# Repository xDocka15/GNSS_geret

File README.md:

# GNSS_Geret_V1

[3D model](https://github.com/xDocka15/GNSS_geret/blob/main/V1/3D_Print/stl/board.stl)

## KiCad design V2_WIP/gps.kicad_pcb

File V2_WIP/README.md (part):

# Zadanie pre GNSS Geret v2025

Dokument popisuje zmeny/upravy v elektronike gnss-geret z 2024 tak aby vznikla
jednodoskova prenostitelna verzia.

## Strucny opis zmien

Cielom je dosiahnut vyssiu integraciu, mensie rozmery a odstranit nedostatky
z predchadzajucej verzie.

Hlavne zmeny:

* \[x] Z troch DPS zredukovat len na jednu dosku.
* \[X] Povodnu hotovu procesorovu dosku FireBeetle2 nahradit samostatnymi obvodmi
  priamo na DPS a usetrit tym miesto:

  * \[x] Pouzit rovnaky ESP32-WROOM-32E modul
  * \[x] USB/UART prevodnik pre programovanie a ladenie ESP32 aj s DTR+RST pre programovanie
  * \[x] Menic napatia z baterie na 3V3
  * \[x] Nabijaci obvod pre bateriu (lepsi ako na FireBeetle2)

* \[x] Doplnit flash pre zaznam dat.
* \[ ] Lepsia citatelnost displeja s casom.

Vacsina suciastok zostava zachovana, zhodna s verziou v2024.

## Nove suciastky

### ESP32

Zvolit modul:

* ESP32-WROVER-E-N16R8 - trosku vacsi rozmer, ale ma vacsiu pamat, vyvody len z dvoch stran.
* \[x] ESP32-WROOM-32E-N16R2 - mensi rozmer, mensia pamat, vyvody z troch stran.

Umiestnit antenou ku okraju DPS. Pod vstavanou antenou je potrebne odstranit
oblast zeme v jednotlivych vrstvach DPS tak aby nedoslo ku zatieneniu anteny (napr.
vrstvou GND, vid. keepout zone v datasheete). Idealne vyfrezovat z plosaku.

Doska WROVER sa pripajkuje priamo na hlavny DPS.

Nerozpustat obsah WROOM modulu priamo na hlavny DPS, odovodnenie:

* nepredpokladam, ze by sa podarilo dosiahnut vasiu mieru integracie ako samotnemu
  vyrobcovi Espressif - t.j. neusetri sa miesto na DPS
* rucne osadzovanie by bolo skoro nemozne
* vyzadovalo by to ozivit zapojenie aj samotneho procesora
* neskor by ake kolvek chyby mohli mat pricinu bud v osadeni alebo navrhu zapojenia
  procesora

### USB/UART prevodnik

Pouzit niektory z casto pouzivanych USB na UART prevodnikov pre ESP procesory.
Napr. CH340K (bol pouzity aj na FireBeetle2) alebo CP2104, ...

Dolezite je pripojit aj DTR a RTS na GPIO0 a RST aby sa dal procesor uviest do
programovacieho rezimu cez USB.

Inspirovat sa zapojenim podla schemy ku FireBeetle2 alebo napr. ku LiLyGo T-Call.

### SPI Flash

Zapracovat "velku" SPI flash, ktora sa bude pouzivat na zaznam udajov z letu.
Napr. 128Mbit (16MB) [Winbond W25Q128FV](https://www.winbond.com/hq/product/code-storage-flash-memory/serial-nor-flash/?__locale=en&partNo=W25Q128FV).
Pripojit na SPI rozhranie.

* \[x] TODO: vyspecifikovat, na ktore piny procesora pripojit. Ktore z dvoch SPI rozhrani je volne?

### Nabijaci resp. power-management modul

Na napajanie bude pouzity jeden clanok Li-Ion baterie (v letectve sa nepouzivaju Li-Pol).
Mal by obsahovat:

* \[x] moznost vycitat cez komunikaciu (idealne I2C) stav nabijania (miera vybita)
* \[x] coulomb counter na meranie kapacity bateria
* \[x] meranie napatia baterie

Zapracovat modul na sledovanie kapacity LiXy batetie MAX17043.
https://techfun.sk/produkt/max17043-i2c-modul-pre-sledovanie-stavu-baterie-1s/

https://www.sparkfun.com/mikroe-charger-2-click.html
Coulomb counter TC3100 + nabijaci obvod IP5306-I2C.
https://electronics.stackexchange.com/questions/17463/help-on-stc3100-calculations
https://github.com/danirebollo/ArduinoSTC3100

* \[x] TODO: upresnit.

### Tlacidlo

Pridat nove mikro-tlacidlo niekam na pravu prednu stranu.

* \[x] TODO: Vyspecifikovat tlacidlo, umiestnenie a pripojenie.

### Indikacna LED

Pridat SMD modru LED na stranu DPS s displejmi. Pouzije sa na zakladnu indikaciu
a ladenie SW. Spolu s LED na rovnaky ovladaci pin procesora pripojit aj test-pad.
Nakolko su vsetky ostatne LED pripojene len cez komunikacne rozhranie, tato bude
urcite fungovat vzdy.
Zapojit na GPIOxy voci GND.

* \[x] TODO: Urcit, na ktory GPIO pin.

### Senzor osvetlenia

Doplnit senzor osvetlenia a automaticky upravovat jas.
Umiestnit ho do vnutorneho rohu kde sa stretava maly dolny displej a stredny velky displej
na pravej strane (na opacnej ako je encoder, aby sa rukou nezakryl).
V kryte sa na danom mieste urobi vybratie, cez ktore (a cez foliu) bude prenikat okolite svetlo
az ku DPS.

* \[x] TODO: Pouzit jednoduchy fototranzistor? Vyspecifikovat.

## Upravy

Vo verzii v2024 boli na DPS/scheme identifikovane nesledujuce body na zlepsenie:

* \[x] Doplnit USB iface pre gnss (3v3 urovne, pripojit vdd\_usb)
  Zvazit umiestnenie plnohodnotneho USB micro-B konektora otoceneho ku okraju DPS
  kvoli servisnemu pristupu do GNSS modulu. Pouzit uhlovy konektor o 90st zarovnany
  s okrajom DPS. Pristupny bude len po vybrati DPS z krabicky.
* \[x] Pridat odrusovaci kondik na tlacidlo tocitka.

  * TODO: Vyspecifikovat.

* \[x] Na vstup A a B z encodra doplnit pull-up rezistory 10k na 3V3.
* \[x] Do footprintu encodera pridat aj diery pre upevnovacie otvory (pajkovatelne, spojene s GND)
* \[x] Pouzit iny typ stredneho 4-ciferneho displeja:

  * Na v2024 bol pouzity typ so spolocnou anodou (KW4-804AGB).

    * Radic HT16K33 je koncipovany tak, ze:
    * cez samostatne anody dokaze do LED pustit 20mA
    * ces spolocnu katodu dokaze preniest 8x 20mA
    * kvoli tomu nebolo mozne vybudit LED na maximalny jas co sa prejavilo na zlej
      citatelnosti za slnecneho svetla.

  * \[x] Vo v2025 pouzit model so spolocnou katodou (KW4-804CGB).

    * Tomu sa musi prisposobit aj zapojenie jednotlivych segmentov (po vzore maleho displeja).
    * \[x] TODO: vyspecifikovat zapojenie displeja.

* \[x] Pouzit USB-C konektor, zapojenie rovnake ako na FireBeetle2.
* \[x] Ku GNSS modulu pripojit aj zalohovaciu bateriu pre RTC.

### Chybajuce veci

Vo verzii v2024 chybali nasledujuce veci, ktore su aplikovatelne aj na v2025:

* \[x] Na 5V vetvu pridat velky stabilizacny kondik 470u/16V.
* Doplnit oznacenie D2 do schemy.
* \[x] Pridat test pad s GND (na pripojenie sondy multimetra/osciloskopu).

### Navrh DPS

Pri navrhu DPS zohladnit nasledujuce pripomienky:

* \[x] Pri ploskach spojenych s GND nastavit uzsie (tensie) mostiky, ktore prepajaju
  plosku s okolitou "vyliatou" plochou, resp. s vrstvou GND. Pri rucnom pajkovani
  sa cez mensie mostiky odvadza menej tepla do susednej velkej medenej plochy
  a suciastky sa lahsie osadzuju.
* \[x] Popisok konektora dat dalej od samotnej suciastky (aby sa po osadeni nezakryl).
* \[x] Zvacsit diery pre hlavny vypinac (bolo treba zbrusit z pinov).

  * \[x] TODO: diery pre kontakty alebo upevnovacie diery?

* \[x] Mensie diery pre kolikove konektory (ak budu pouzite, boli volne a dali sa osadit krivo :)
* \[x] Doplnit popisky ku test-padom "TPx" aby sa dali lahsie sparovat so schemou.
* \[ ] Pri vyrobe pouzit ciernu farbu plosaku, nie zelenu. Cierne pozadie zlepsi
  citatelnost 7-seg displejov.
* \[x] Niektore TP presunut ku okrajom DPS, tak aby boli dostupne z oboch stran DPS
  a neboli zakryte suciastkami (napr. displejmi):

  * TP6 (5V)
  * TPxy (3V3, pridat)
  * TPxy (GND, pridat)

* \[x] Antenny konektor moze byt bud SMA alebo U.FL (IPEX)

  * Na DPS cez seba prekryt plosky pre oba typy konektorov
  * Vid. footprint: https://meshtastic.org/assets/images/t-beam-sx1262-3dc0a8d2d866b06b04a457567063e034.webp
  * Bud sa osadi SMA konektor (uhlovy alebo priamy) alebo sa osadi U.FL konektor
    a antena sa zabuduje priamo do skatulky.

* Pri rozmiestnovani suciastok je mozne umiestnit niektore aj pod maly dolny
  displej z TOP strany.

  * Aby bol displej v rovine s RGB displejmi, musi byt osadeny co najdalej od DPS.
  * Tym vznikne pod displejom pohodlny priestor pre SMD rezistory, kondiky, atp...

    * \[ ] TODO: zmerat vzdialenost od DPS po display.

## Mechanicke upravy

* Zachovat rozostup aj velkosti montaznych dier v troch rohoch.

  * Pouziju sa bud na uchytenie do pristrojoveho panela v lietadle alebo na
    uchytenie krabicky.

* Ine montazne diery nebudu potrebne. Bateria sa osadi do drziaka v krabicke.
* Zachovat umiestnenie antenneho konektora GPS na okraji plosaku aby sa mohol
  pouzit aj uhlovy konektor a externa antena.

# Pripomienky k v2024

Releventnost nasledujuce pripomienok ku verzii v2024 a ich aplikovatelnost aj na
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
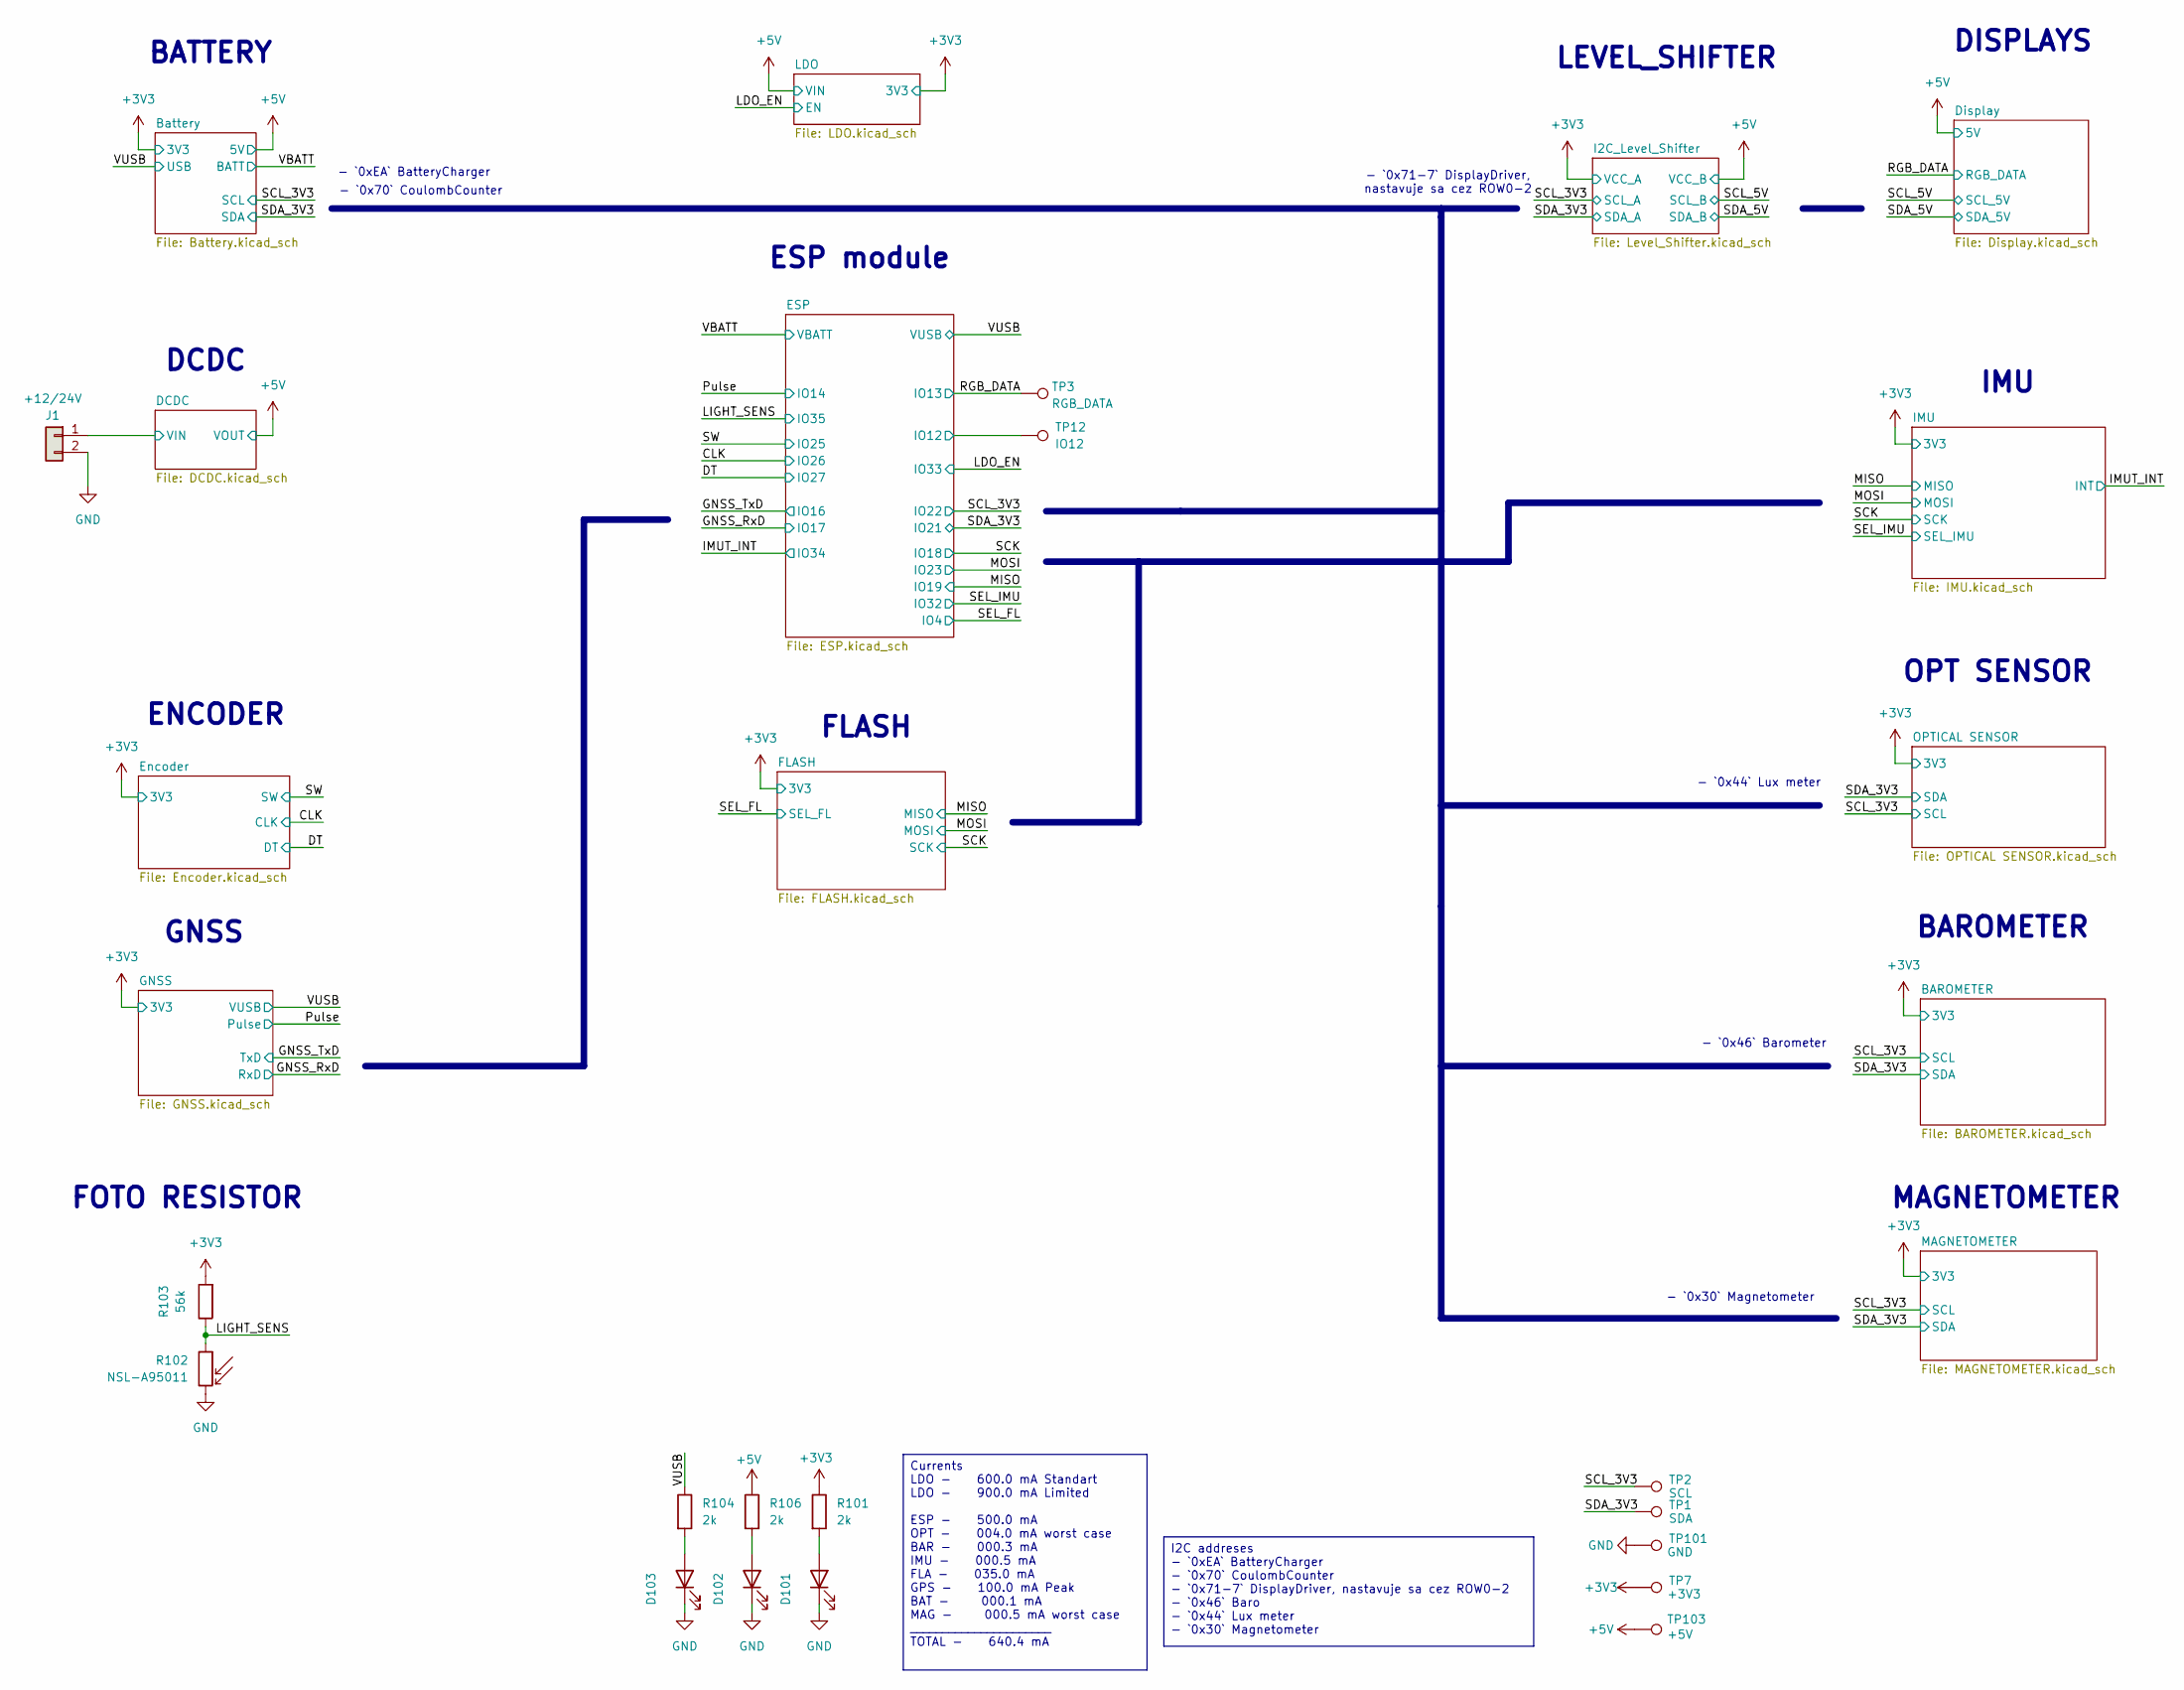
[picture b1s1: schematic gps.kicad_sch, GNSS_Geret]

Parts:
D101, D102, D103: D_0603_1608Metric_Pad1.05x0.95mm_HandSolder
J1: +12/24V; PhoenixContact_GMSTBVA_2,5_2-G-7,62_1x02_P7.62mm_Vertical
R101, R104, R106: 2k; R_0603_1608Metric_Pad0.98x0.95mm_HandSolder
R102: NSL-A95011; R_LDR_5.1x4.3mm_P3.4mm_Vertical
R103: 56k; R_0603_1608Metric_Pad0.98x0.95mm_HandSolder
TP1: SDA; TestPoint_Pad_D1.0mm
TP2: SCL; TestPoint_Pad_D1.0mm
TP3: RGB_DATA; TestPoint_Pad_D1.0mm
TP7: +3V3; TestPoint_Pad_D1.0mm
TP12: IO12; TestPoint_Pad_D1.0mm
TP101: GND; TestPoint_THTPad_D2.5mm_Drill1.2mm
TP103: +5V; TestPoint_Pad_D1.0mm

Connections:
+3V3: R101.1, R103.2, TP7.1 (1_1); also elsewhere on the board
+5V: R106.1, TP103.1 (1_1); also elsewhere on the board
/DCDC/VIN: J1.1; also elsewhere on the board
/ESP/IO12: TP12.1 (1_1); also elsewhere on the board
/LIGHT_SENS: R102.1, R103.1; also elsewhere on the board
/RGB_DATA: TP3.1 (1_1); also elsewhere on the board
/SCL_3V3: TP2.1 (1_1); also elsewhere on the board
/SDA_3V3: TP1.1 (1_1); also elsewhere on the board
/VUSB: R104.1; also elsewhere on the board
GND: D101.1 (K), D102.1 (K), D103.1 (K), J1.2, R102.2, TP101.1 (1_1); also elsewhere on the board
unnamed: D101.2 (A), R101.2
unnamed: D102.2 (A), R106.2
unnamed: D103.2 (A), R104.2

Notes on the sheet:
ESP module
- `0x44` Lux meter
BATTERY
GNSS
DCDC
OPT SENSOR
MAGNETOMETER
FOTO RESISTOR
FLASH
DISPLAYS
- `0xEA` BatteryCharger
- `0x71-7` DisplayDriver, nastavuje sa cez ROW0-2
- `0x46` Barometer
BAROMETER
- `0x70` CoulombCounter
- `0x30` Magnetometer
ENCODER
LEVEL_SHIFTER
IMU
Currents LDO - 600.0 mA Standart LDO - 900.0 mA Limited ESP - 500.0 mA OPT - 004.0 mA worst case BAR - 000.3 mA IMU - 000.5 mA FLA - 035.0 mA GPS - 100.0 mA Peak BAT - 000.1 mA MAG - 000.5 mA worst case ______________________ TOTAL - 640.4 mA
I2C addreses - `0xEA` BatteryCharger - `0x70` CoulombCounter - `0x71-7` DisplayDriver, nastavuje sa cez ROW0-2 - `0x46` Baro - `0x44` Lux meter - `0x30` Magnetometer

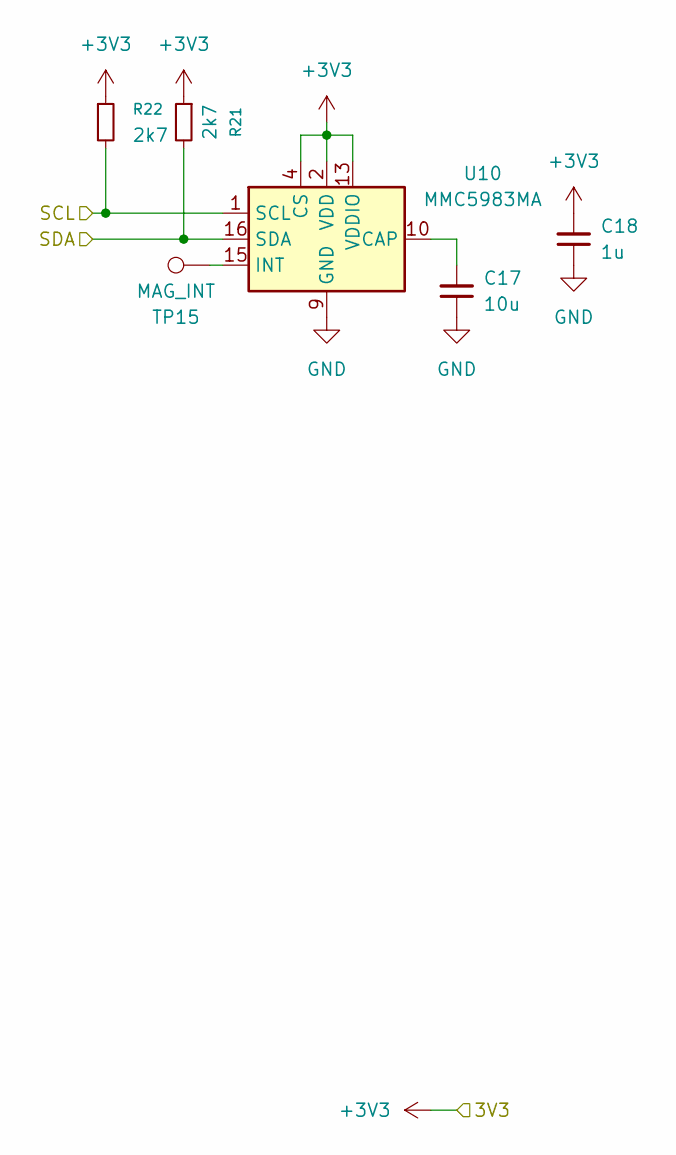
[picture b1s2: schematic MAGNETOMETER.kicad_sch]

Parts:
C17: 10u; C_0603_1608Metric_Pad1.08x0.95mm_HandSolder
C18: 1u; C_0603_1608Metric_Pad1.08x0.95mm_HandSolder
R21, R22: 2k7; R_0603_1608Metric_Pad0.98x0.95mm_HandSolder
TP15: MAG_INT; TestPoint_Pad_D1.0mm
U10: MMC5983MA; LGA-16_3x3mm_P0.5mm

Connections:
+3V3: C18.2, R21.1, R22.1, U10.2 (VDD), U10.4 (CS), U10.13 (VDDIO); also elsewhere on the board
/SCL_3V3: R22.2, U10.1 (SCL); also elsewhere on the board
/SDA_3V3: R21.2, U10.16 (SDA); also elsewhere on the board
GND: C17.1, C18.1, U10.9 (GND), U10.11 (GND); also elsewhere on the board
unnamed: C17.2, U10.10 (CAP)
unnamed: TP15.1 (1_1), U10.15 (INT)

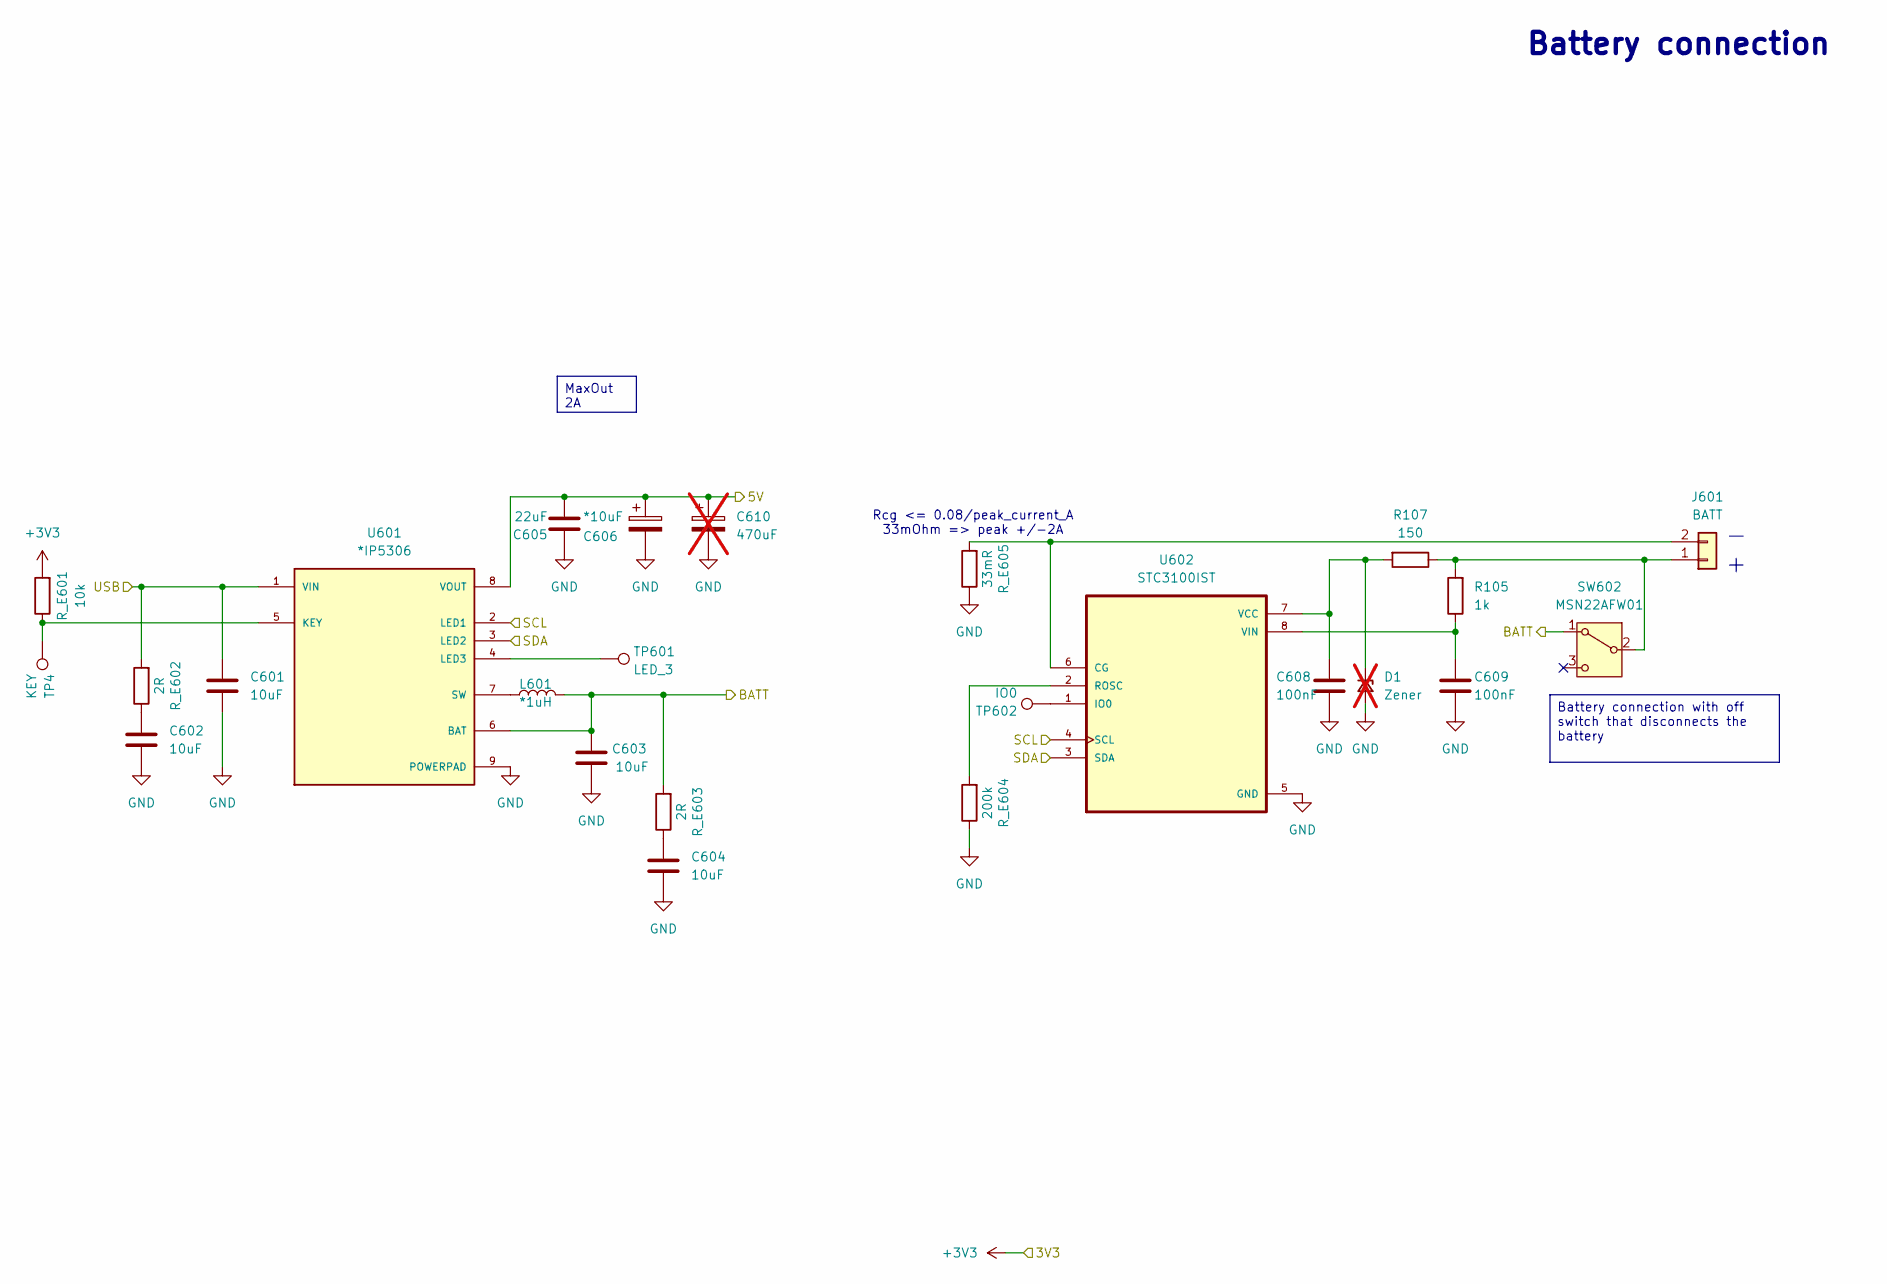
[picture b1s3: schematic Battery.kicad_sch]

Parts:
C601, C602, C603, C604: 10uF; C_0603_1608Metric_Pad1.08x0.95mm_HandSolder
C605: 22uF; C_0603_1608Metric_Pad1.08x0.95mm_HandSolder
C606: *10uF; CP_EIA-3528-21_Kemet-B_HandSolder
C608, C609: 100nF; C_0603_1608Metric_Pad1.08x0.95mm_HandSolder
C610: 470uF; C_Elec_6.3x7.7; not fitted
D1: Zener; D_SOD-523; not fitted
J601: BATT; Molex_PicoBlade_53398-0271_1x02-1MP_P1.25mm_Vertical
L601: *1uH; L_1008_2520Metric_Pad1.43x2.20mm_HandSolder
R105: 1k; R_0603_1608Metric_Pad0.98x0.95mm_HandSolder
R107: 150; R_0603_1608Metric_Pad0.98x0.95mm_HandSolder
R_E601: 10k; R_0603_1608Metric_Pad0.98x0.95mm_HandSolder
R_E602, R_E603: 2R; R_0603_1608Metric_Pad0.98x0.95mm_HandSolder
R_E604: 200k; R_0603_1608Metric_Pad0.98x0.95mm_HandSolder
R_E605: 33mR; R_0603_1608Metric_Pad0.98x0.95mm_HandSolder
SW602: MSN22AFW01
TP4: KEY; TestPoint_Pad_D1.0mm
TP601: LED_3; TestPoint_Pad_D1.0mm
TP602: IO0; TestPoint_Pad_D1.0mm
U601: *IP5306; SOP127P600X165-9N; PARTREV 1.31
U602: STC3100IST; SOIC65P490X110-8N

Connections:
+3V3: R_E601.2; also elsewhere on the board
+5V: C605.2, C606.1, C610.1, U601.8 (VOUT); also elsewhere on the board
/SCL_3V3: U601.2 (LED1), U602.4 (SCL); also elsewhere on the board
/SDA_3V3: U601.3 (LED2), U602.3 (SDA); also elsewhere on the board
/VBATT: C603.1, L601.2, R_E603.2, SW602.1 (A), U601.6 (BAT); also elsewhere on the board
/VUSB: C601.1, R_E602.2, U601.1 (VIN); also elsewhere on the board
GND: C601.2, C602.2, C603.2, C604.2, C605.1, C606.2, C608.2, C609.2, C610.2, D1.2 (A), R_E604.1, R_E605.1, U601.9 (POWERPAD), U602.5 (GND); also elsewhere on the board
unnamed: C602.1, R_E602.1
unnamed: C604.1, R_E603.1
unnamed: C608.1, D1.1 (K), R107.2, U602.7 (VCC)
unnamed: J601.1, R105.2, R107.1, SW602.2 (B)
unnamed: J601.2, R_E605.2, U602.6 (CG)
unnamed: R_E601.1, TP4.1 (1_1), U601.5 (KEY)
unnamed: TP601.1 (1_1), U601.4 (LED3)
unnamed: L601.1, U601.7 (SW)
unnamed: TP602.1 (1_1), U602.1 (IO0)
unnamed: R_E604.2, U602.2 (ROSC)
unnamed: C609.1, R105.1, U602.8 (VIN)

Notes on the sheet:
- +
Battery connection
Rcg <= 0.08/peak_current_A 33mOhm => peak +/-2A
MaxOut 2A
Battery connection with off switch that disconnects the battery

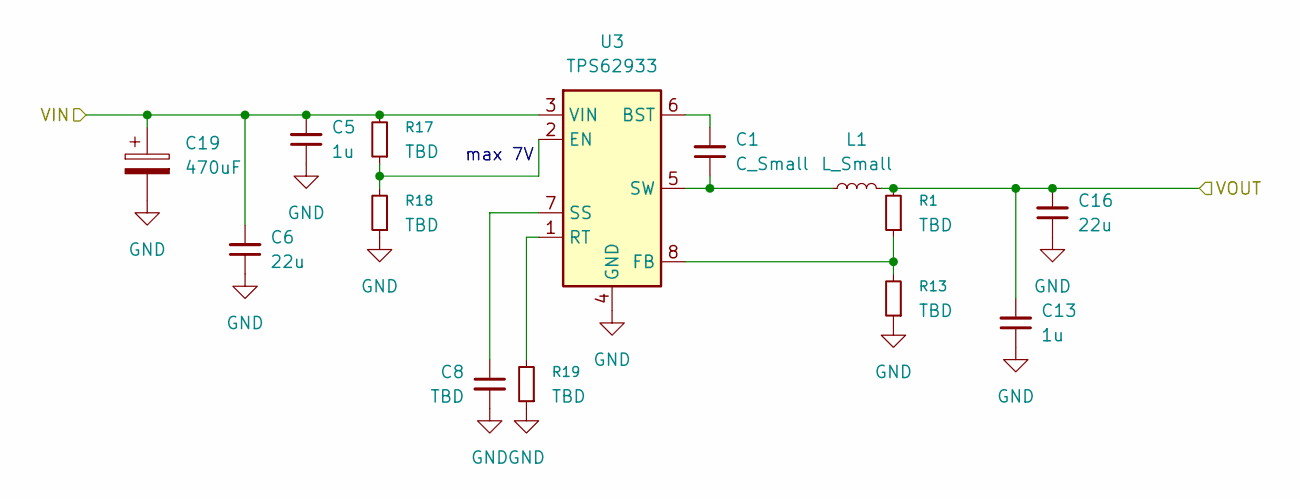
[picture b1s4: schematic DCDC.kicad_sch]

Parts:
C1: C_Small; C_0603_1608Metric_Pad1.08x0.95mm_HandSolder
C5, C13: 1u; C_0603_1608Metric_Pad1.08x0.95mm_HandSolder
C6, C16: 22u; C_0805_2012Metric_Pad1.18x1.45mm_HandSolder
C8: TBD; C_0603_1608Metric_Pad1.08x0.95mm_HandSolder
C19: 470uF; C_Elec_6.3x7.7
L1: L_Small; L_Wuerth_XHMI-6060
R1, R13, R17, R18, R19: TBD; R_0603_1608Metric_Pad0.98x0.95mm_HandSolder
U3: TPS62933; SOT-583-8

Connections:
+5V: C13.2, C16.2, L1.2, R1.2; also elsewhere on the board
/DCDC/VIN: C5.2, C6.2, C19.1, R17.2, U3.3 (VIN); also elsewhere on the board
GND: C5.1, C6.1, C8.2, C13.1, C16.1, C19.2, R13.1, R18.1, R19.1, U3.4 (GND); also elsewhere on the board
unnamed: C1.2, U3.6 (BST)
unnamed: R17.1, R18.2, U3.2 (EN)
unnamed: R1.1, R13.2, U3.8 (FB)
unnamed: R19.2, U3.1 (RT)
unnamed: C8.1, U3.7 (SS)
unnamed: C1.1, L1.1, U3.5 (SW)

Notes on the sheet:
max 7V

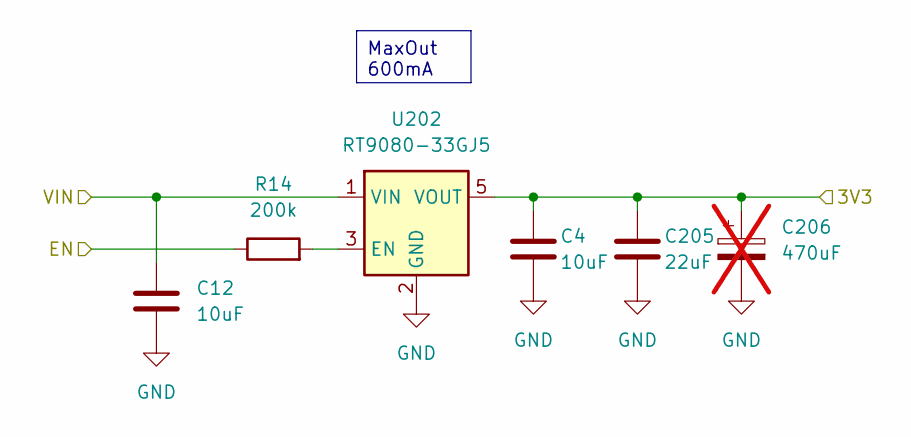
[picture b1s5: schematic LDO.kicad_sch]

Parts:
C4, C12: 10uF; C_0603_1608Metric_Pad1.08x0.95mm_HandSolder
C205: 22uF; C_0603_1608Metric_Pad1.08x0.95mm_HandSolder
C206: 470uF; C_Elec_6.3x7.7; not fitted
R14: 200k; R_0603_1608Metric_Pad0.98x0.95mm_HandSolder
U202: RT9080-33GJ5; SOT-23-5_HandSoldering

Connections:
+3V3: C4.1, C205.1, C206.1, U202.5 (VOUT); also elsewhere on the board
+5V: C12.1, U202.1 (VIN); also elsewhere on the board
/LDO_EN: R14.1; also elsewhere on the board
GND: C4.2, C12.2, C205.2, C206.2, U202.2 (GND); also elsewhere on the board
unnamed: R14.2, U202.3 (EN)

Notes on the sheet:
MaxOut 600mA

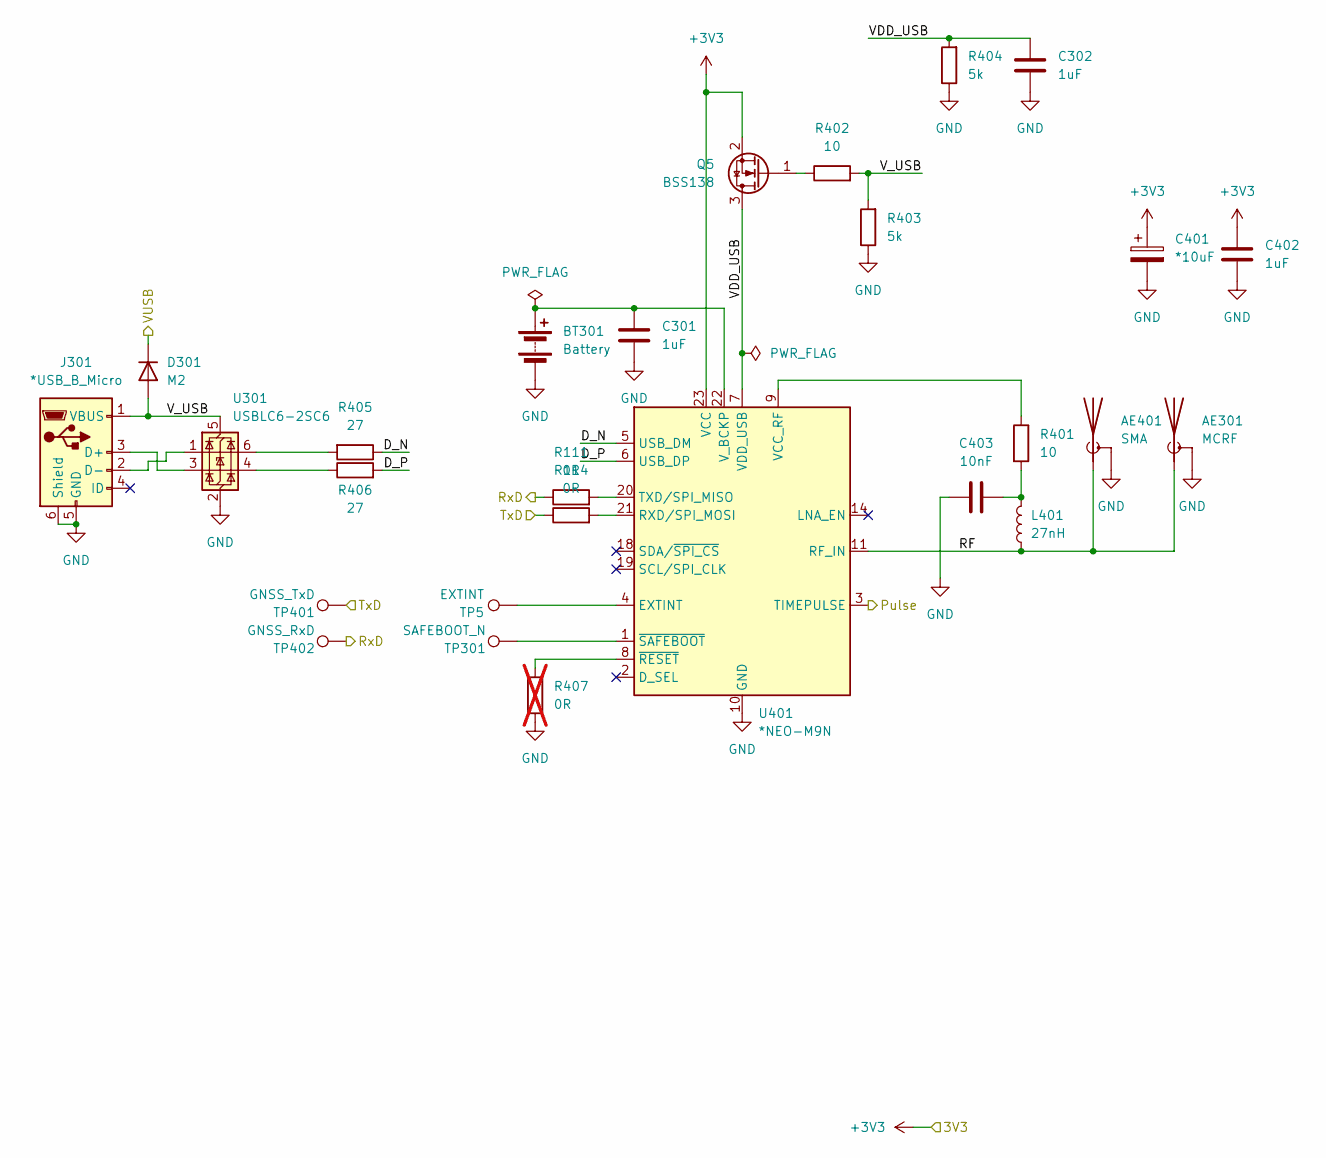
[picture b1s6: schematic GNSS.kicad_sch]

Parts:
AE301: MCRF; U.FL_Molex_MCRF_73412-0110_Vertical
AE401: SMA; lemo_epb00250ntn
BT301: Battery; BatteryHolder_MPD_BC2003_1x2032
C301, C302, C402: 1uF; C_0603_1608Metric_Pad1.08x0.95mm_HandSolder
C401: *10uF; CP_EIA-3528-21_Kemet-B_HandSolder
C403: 10nF; C_0805_2012Metric_Pad1.18x1.45mm_HandSolder
D301: M2; D_SMA
J301: *USB_B_Micro; 629105150521
L401: 27nH; L_0402_1005Metric_Pad0.77x0.64mm_HandSolder
Q5: BSS138; SOT-23
R111, R114: 0R; R_0603_1608Metric_Pad0.98x0.95mm_HandSolder
R401: 10; R_1206_3216Metric_Pad1.30x1.75mm_HandSolder
R402: 10; R_0603_1608Metric_Pad0.98x0.95mm_HandSolder
R403, R404: 5k; R_0603_1608Metric_Pad0.98x0.95mm_HandSolder
R405, R406: 27; R_0603_1608Metric_Pad0.98x0.95mm_HandSolder
R407: 0R; R_0603_1608Metric_Pad0.98x0.95mm_HandSolder; not fitted
TP5: EXTINT; TestPoint_Pad_D1.0mm
TP301: SAFEBOOT_N; TestPoint_Pad_D1.0mm
TP401: GNSS_TxD; TestPoint_Pad_D1.0mm
TP402: GNSS_RxD; TestPoint_Pad_D1.0mm
U301: USBLC6-2SC6; SOT-23-6
U401: *NEO-M9N; ublox_NEO

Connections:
+3V3: C401.1, C402.1, Q5.2 (S), U401.23 (VCC); also elsewhere on the board
/GNSS/D_N: R405.1, U401.5 (USB_DM)
/GNSS/D_P: R406.2, U401.6 (USB_DP)
/GNSS/RF: AE301.1 (A), AE401.1 (A), L401.1, U401.11 (RF_IN)
/GNSS/VDD_USB: C302.1, Q5.3 (D), R404.2, U401.7 (VDD_USB)
/GNSS/V_USB: D301.2 (A), J301.1 (VBUS), R402.2, R403.2, U301.5 (VBUS)
/GNSS_RxD: R111.1, TP402.1 (1_1); also elsewhere on the board
/GNSS_TxD: R114.1, TP401.1 (1_1); also elsewhere on the board
/Pulse: U401.3 (TIMEPULSE); also elsewhere on the board
/VUSB: D301.1 (K); also elsewhere on the board
GND: AE301.2 (Shield), AE401.2 (Shield), BT301.2 (-), C301.2, C302.2, C401.2, C402.2, C403.1, J301.5 (GND), J301.6 (Shield), R403.1, R404.1, R407.1, U301.2 (GND), U401.10 (GND), U401.12 (GND), U401.13 (GND), U401.24 (GND); also elsewhere on the board
unnamed: BT301.1 (+), C301.1, U401.22 (V_BCKP)
unnamed: C403.2, L401.2, R401.2
unnamed: J301.3 (D+), U301.3 (I/O2)
unnamed: J301.2 (D-), U301.1 (I/O1)
unnamed: Q5.1 (G), R402.1
unnamed: R405.2, U301.6 (I/O1)
unnamed: R406.1, U301.4 (I/O2)
unnamed: TP5.1 (1_1), U401.4 (EXTINT)
unnamed: R114.2, U401.21 (RXD/SPI_MOSI)
unnamed: R111.2, U401.20 (TXD/SPI_MISO)
unnamed: R401.1, U401.9 (VCC_RF)
unnamed: R407.2, U401.8 (~RESET)
unnamed: TP301.1 (1_1), U401.1 (~SAFEBOOT)

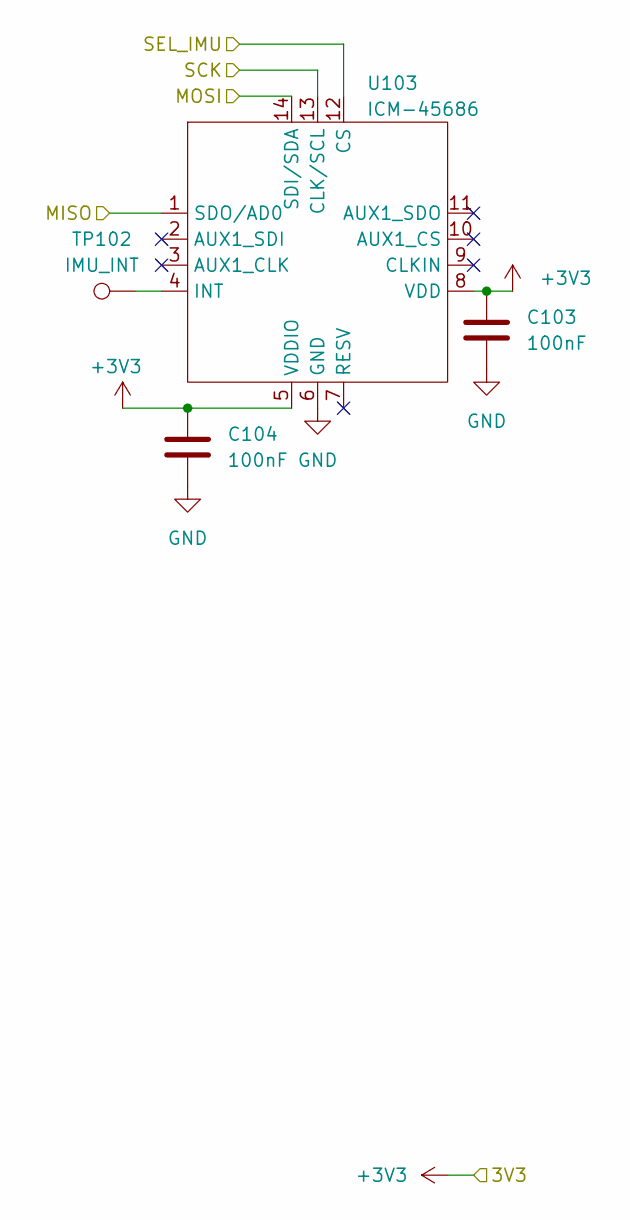
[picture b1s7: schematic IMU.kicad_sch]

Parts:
C103, C104: 100nF; C_0603_1608Metric_Pad1.08x0.95mm_HandSolder
TP102: IMU_INT; TestPoint_Pad_D1.0mm
U103: ICM-45686; LGA-14_3x2.5mm_P0.5mm_LayoutBorder3x4y

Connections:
+3V3_ESP: C103.2, C104.2, U103.5 (VDDIO), U103.8 (VDD); also elsewhere on the board
/MISO: U103.1 (SDO/AD0); also elsewhere on the board
/MOSI: U103.14 (SDI/SDA); also elsewhere on the board
/SCK: U103.13 (CLK/SCL); also elsewhere on the board
/SEL_IMU: U103.12 (CS); also elsewhere on the board
GND: C103.1, C104.1, U103.6 (GND); also elsewhere on the board

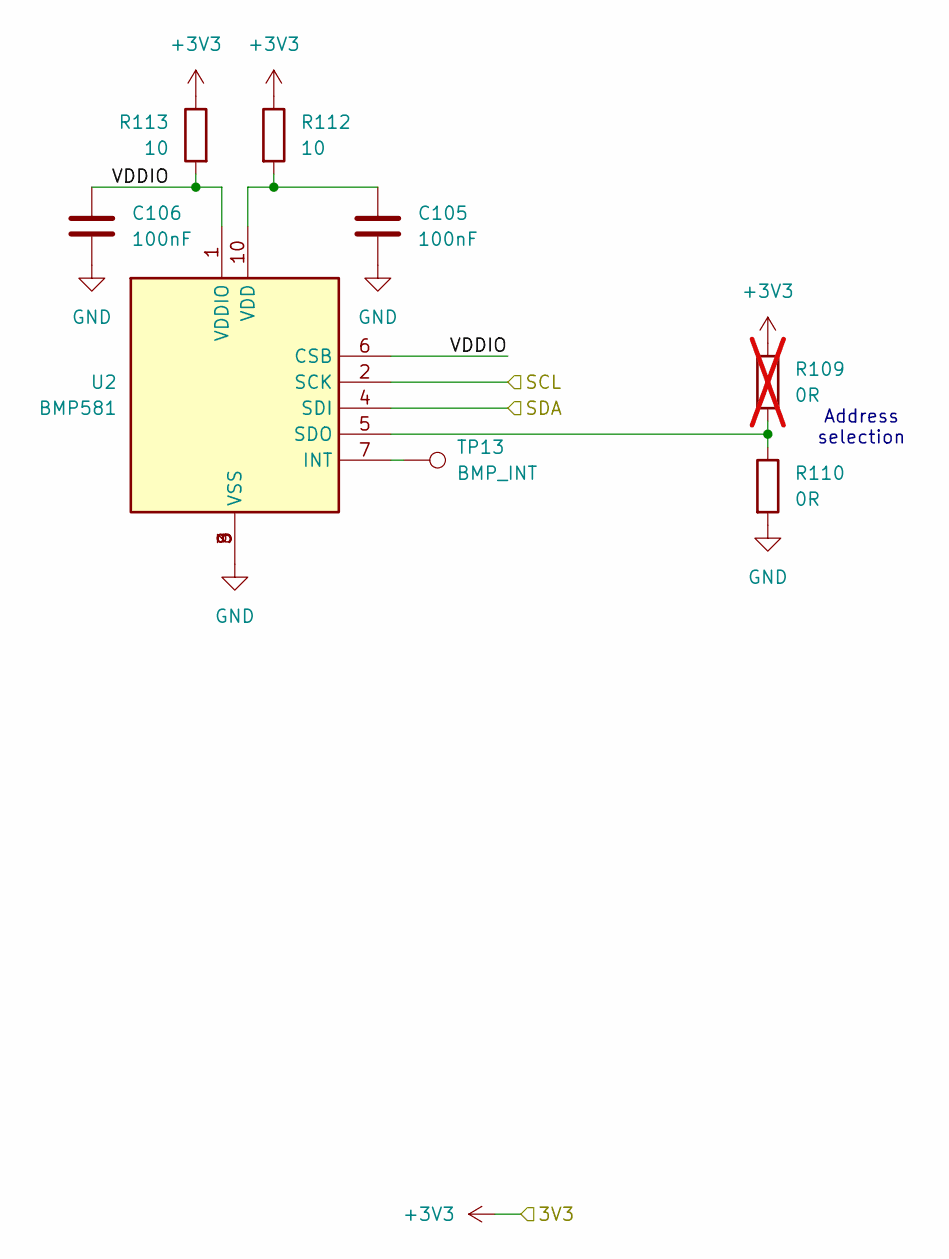
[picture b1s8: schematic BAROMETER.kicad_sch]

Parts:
C105, C106: 100nF; C_0603_1608Metric_Pad1.08x0.95mm_HandSolder
R109: 0R; R_0603_1608Metric_Pad0.98x0.95mm_HandSolder; not fitted
R110: 0R; R_0603_1608Metric_Pad0.98x0.95mm_HandSolder
R112, R113: 10; R_0603_1608Metric_Pad0.98x0.95mm_HandSolder
TP13: BMP_INT; TestPoint_Pad_D1.0mm
U2: BMP581; Mouser Part Number 262-BMP581

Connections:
+3V3: R109.1, R112.1, R113.1; also elsewhere on the board
/BAROMETER/VDDIO: C106.2, R113.2, U2.1 (VDDIO), U2.6 (CSB)
/SCL_3V3: U2.2 (SCK); also elsewhere on the board
/SDA_3V3: U2.4 (SDI); also elsewhere on the board
GND: C105.1, C106.1, R110.2, U2.3 (VSS), U2.8 (VSS), U2.9 (VSS); also elsewhere on the board
unnamed: TP13.1 (1_1), U2.7 (INT)
unnamed: R109.2, R110.1, U2.5 (SDO)
unnamed: C105.2, R112.2, U2.10 (VDD)

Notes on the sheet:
Address selection

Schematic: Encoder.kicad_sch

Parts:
C701: 100nF; C_0603_1608Metric_Pad1.08x0.95mm_HandSolder
C702, C703: 1nF; C_0603_1608Metric_Pad1.08x0.95mm_HandSolder
R_E701, R_E702, R_E704: 10k; R_0603_1608Metric_Pad0.98x0.95mm_HandSolder
R_E703: 2k; R_0603_1608Metric_Pad0.98x0.95mm_HandSolder
R_E705, R_E706: 47; R_0603_1608Metric_Pad0.98x0.95mm_HandSolder
SW701: *RotaryEncoder; RotaryEncoder_Alps_EC12E-Switch_Vertical_H20mm_CircularMoun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
TP701: CLK; TestPoint_Pad_D1.0mm
TP702: DT; TestPoint_Pad_D1.0mm

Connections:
+3V3: R_E701.2, R_E702.2, R_E704.2; also elsewhere on the board
/CLK: C703.1, R_E702.1, R_E705.1, TP701.1 (1_1); also elsewhere on the board
/DT: C702.1, R_E704.1, R_E706.1, TP702.1 (1_1); also elsewhere on the board
/SW: C701.1, R_E703.2; also elsewhere on the board
GND: C701.2, C702.2, C703.2, SW701.C, SW701.S2; also elsewhere on the board
unnamed: R_E701.1, R_E703.1, SW701.S1
unnamed: R_E705.2, SW701.A
unnamed: R_E706.2, SW701.B

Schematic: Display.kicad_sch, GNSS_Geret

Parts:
C7, C9, C404, C405, C406: 100nF; C_0603_1608Metric_Pad1.08x0.95mm_HandSolder
D8: 1N4148W-G3-08; D_SOD-123
DS1: LTC-4724JF; LTC4724JF; Mouser Part Number 859-LTC-4724JF
R_E103, R_E104, R_E105, R_E106, R_E107, R_E108, R_E109, R_E110: 0R; R_0603_1608Metric_Pad0.98x0.95mm_HandSolder
R_E111, R_E112, R_E113: 39k; R_0603_1608Metric_Pad0.98x0.95mm_HandSolder; not fitted
TP403: RGB_5V; TestPoint_Pad_D1.0mm
U4: *HT16k33; SOIC-28W_7.5x17.9mm_P1.27mm
U5, U6, U7: *7seg_1x1_rgb; 7seg_1x1_rgb
U11: *SN74LV1T34DBVRG4; SOT-23-5
U402: *KW4-804CGB; 7seg_4x1

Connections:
+5V: C7.1, C9.2, C404.2, C405.2, C406.2, U4.28 (VDD), U5.1 (VCC), U6.1 (VCC), U7.1 (VCC), U11.5 (VCC); also elsewhere on the board
/Display/CC1: R_E104.1, U4.6 (COM4)
/Display/CC2: R_E105.1, U4.7 (COM5)
/Display/CC3: R_E106.1, U4.8 (COM6)
/Display/CC11: D8.2 (A), R_E107.2, U4.2 (COM0/AD)
/Display/CC22: R_E108.2, U4.3 (COM1/KS0)
/Display/CC33: R_E109.2, U4.4 (COM2/KS1)
/Display/CC44: R_E110.2, U4.5 (COM3/KS2)
/Display/CCL123: R_E103.2, U4.9 (COM7)
/Display/DP: DS1.6 (ANODE_DP), U4.18 (ROW7/K5), U402.3 (DPX)
/Display/a: DS1.12 (ANODE_AL1), R_E111.1, U4.25 (ROW0/A2), U402.11 (a)
/Display/b: DS1.11 (ANODE_BL2), R_E112.1, U4.24 (ROW1/A1), U402.7 (b)
/Display/c: DS1.3 (ANODE_CL3), R_E113.1, U4.23 (ROW2/A0), U402.4 (c)
/Display/d: DS1.4 (ANODE_D), U4.22 (ROW3/K1), U402.2 (d)
/Display/e: DS1.2 (ANODE_E), U4.21 (ROW4/K2), U402.1 (e)
/Display/f: DS1.15 (ANODE_F), U4.20 (ROW5/K3), U402.10 (f)
/Display/g: DS1.8 (ANODE_G), U4.19 (ROW6/K4), U402.5 (g)
/RGB_DATA: U11.2 (A); also elsewhere on the board
/SCL_5V: U4.26 (SCL); also elsewhere on the board
/SDA_5V: U4.27 (SDA); also elsewhere on the board
GND: C7.2, C9.1, C404.1, C405.1, C406.1, U4.1 (VSS), U5.3 (GND), U6.3 (GND), U7.3 (GND), U11.3 (GND); also elsewhere on the board
unnamed: D8.1 (K), R_E111.2, R_E112.2, R_E113.2
unnamed: DS1.1 (COMMON_CATHODE_DIGIT_1), R_E104.2
unnamed: DS1.5 (COMMON_CATHODE_DIGIT_2), R_E105.2
unnamed: DS1.7 (COMMON_CATHODE_DIGIT_3), R_E106.2
unnamed: DS1.14 (COMMON_CATHODE__L1L2L3), R_E103.1
unnamed: U5.5 (DO), U6.2 (DI)
unnamed: U6.5 (DO), U7.2 (DI)
unnamed: TP403.1 (1_1), U5.2 (DI), U11.4 (Y)
unnamed: R_E107.1, U402.12 (CC1)
unnamed: R_E108.1, U402.9 (CC2)
unnamed: R_E109.1, U402.8 (CC3)
unnamed: R_E110.1, U402.6 (CC4)

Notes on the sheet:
RGB 7seg displays
7seg displays and 7seg driver
ROW+ anode COM- cathode
